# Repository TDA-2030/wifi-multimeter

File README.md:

# WiFi Multimeter

A mini multimeter based on ESP32, that display the result on web page.

## Features

- Web page as monitor

- Portable, small size

- Voice announcements

## Functions

  - voltage: ±400V, ±60V, ±2V

  - current: ±10A, ±2A, ±10mA

  - resistance: 1KΩ, 200KΩ, 10MΩ

  - buzzer

  - power
  
  - diode drop voltage

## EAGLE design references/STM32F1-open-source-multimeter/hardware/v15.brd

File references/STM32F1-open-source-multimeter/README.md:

# STM32 OpenSource Multimeter
*see the article [here](http://embedblog.eu/?p=438) or the video [here](https://youtu.be/qQX5iS70-mg)*

## Specs (revision 1.5 - latest stable)
1. voltage measurement: ±60 V, ±6 V, ±600 mV, ±60 m ranges, with DC or RMS data acquisition
2. current measurement: ±250 or ±2500 mA ranges, again with DC or RMS
3. can measure voltage and current simultaneously and display the product, ie power
4. measures continuity and displays the resistance and voltage drop
5. can perform simple component testing
6. frequency measurement up to 10 MHz

Additional features: isolated USB serial port; ; 2 kB EEPROM; 4 bit expansion port; battery voltage measurement & charging via USB; firmware update via USB; integrated kickstand; hold function

*Note: when this project started, it used STM32F1. Now it uses STM32F3, but I cannot rename the repository, so I hope it won't mislead anyone.*

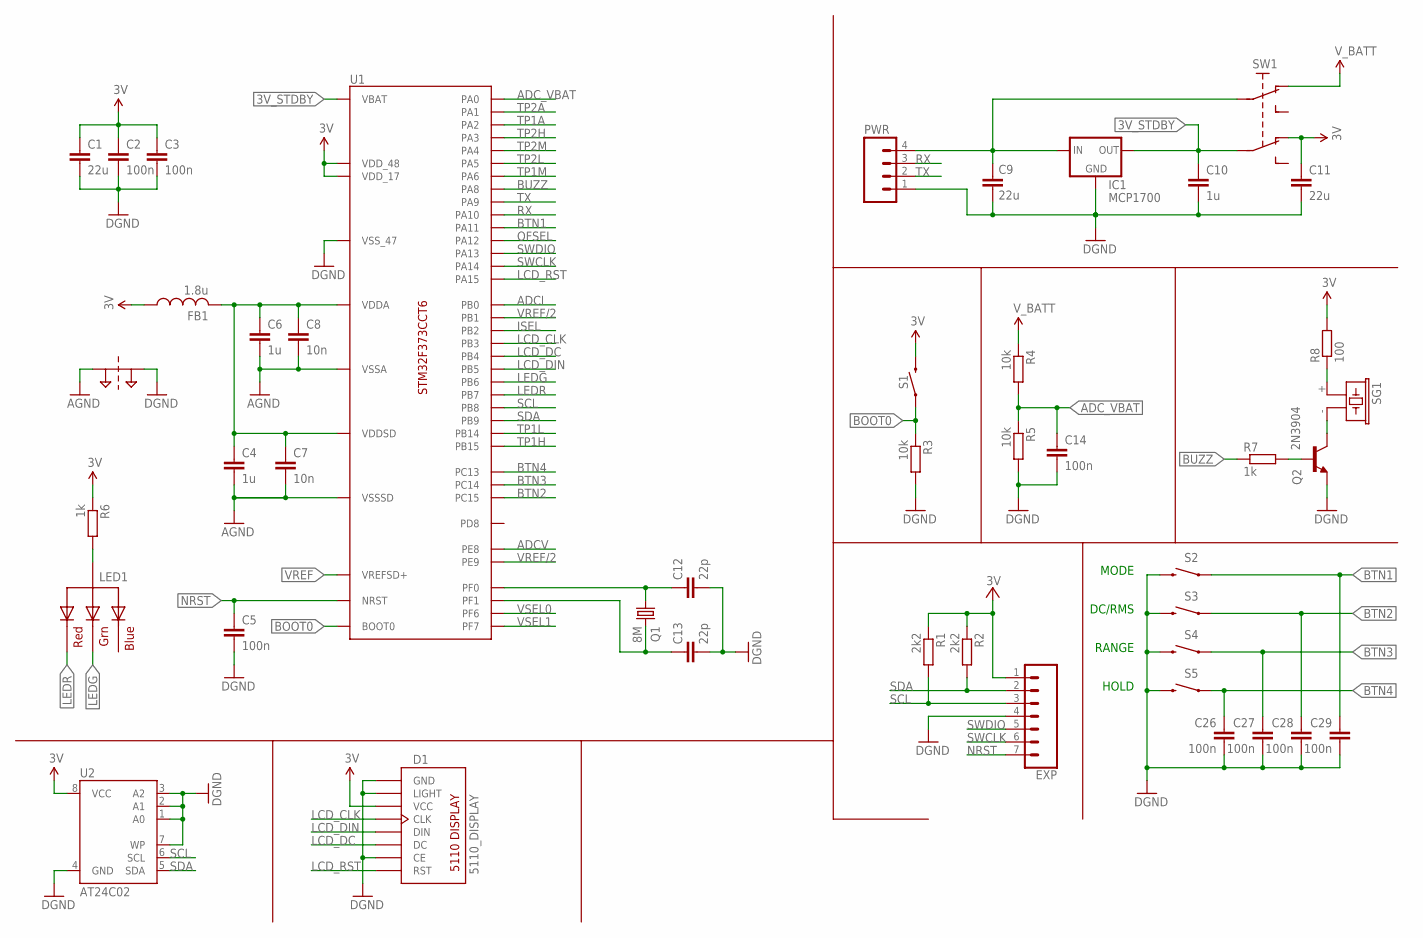
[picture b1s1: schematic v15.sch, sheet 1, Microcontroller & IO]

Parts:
C1, C9, C11: 22u; C1206
C2, C3, C5, C14, C26, C27, C28, C29: 100n; C1206
C4, C6, C10: 1u; C1206
C7, C8: 10n; C1206
C12, C13: 22p; C1206
D1: 5110_DISPLAY; 5110_LAYOUT
EXP: CONN_07; 1X07
FB1: 1.8u; 1206
IC1: MCP1700; SOT23
LED1: RGBLED_CA-5MM; LED5MMRGB
PT1: 2PT_GND_TIE
PWR: M04PTH; 1X04@1
Q1: 8M; HC49U-V
Q2: 2N3904; SOT23
R1, R2: 2k2; R1206
R3, R4, R5: 10k; R1206
R6, R7: 1k; R1206
R8: 100; R1206
S1: MOMENTARY-SWITCH-SPST-PTH-6.0MM; TACTILE_SWITCH_PTH_6.0MM
S2, S3, S4, S5: MOMENTARY-SWITCH-SPST-SMD-12MM; TACTILE_SWITCH_SMD_12MM
SG1: F/CM12P
SW1: DPDT_SWITCH_SMALL; DPDT_SMALL
U1: STM32F373CCT6; LQFP-48
U2: AT24C02; SOIC8

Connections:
3V: C1.1, C2.1, C3.1, C11.1, D1.VCC, EXP.1, FB1.1, R1.1, R2.1, R6.1, R8.2, S1.3 (2), SW1.P$6 (NC2), U1.17 (VDD_17), U1.48 (VDD_48), U2.8 (VCC); also elsewhere on the board
3V_STDBY: C10.1, IC1.2 (OUT), SW1.P$5 (I2), U1.1 (VBAT)
ADCI: U1.18 (PB0); also elsewhere on the board
ADCV: U1.21 (PE8); also elsewhere on the board
ADC_VBAT: C14.1, R4.2, R5.1, U1.10 (PA0)
AGND: C4.2, C6.2, C7.2, C8.2, PT1.P$1, U1.8 (VSSA), U1.23 (VSSSD); also elsewhere on the board
BOOT0: R3.1, S1.1, U1.44 (BOOT0)
BTN1: C29.1, S2.1, U1.32 (PA11)
BTN2: C28.1, S3.1, U1.4 (PC15)
BTN3: C27.1, S4.1, U1.3 (PC14)
BTN4: C26.1, S5.1, U1.2 (PC13)
BUZZ: R7.1, U1.29 (PA8)
GND: C1.2, C2.2, C3.2, C5.2, C9.2, C10.2, C11.2, C12.2, C13.2, C14.2, C26.2, C27.2, C28.2, C29.2, D1.CE, D1.GND, D1.LIGHT, EXP.4, IC1.1 (GND), PT1.P$2, PWR.1, Q2.2 (E), R3.2, R5.2, S2.3 (2), S3.3 (2), S4.3 (2), S5.3 (2), U1.47 (VSS_47), U2.1 (A0), U2.2 (A1), U2.3 (A2), U2.4 (GND), U2.7 (WP)
ISEL: U1.20 (PB2); also elsewhere on the board
LCD_CLK: D1.CLK, U1.39 (PB3)
LCD_DC: D1.DC, U1.40 (PB4)
LCD_DIN: D1.DIN, U1.41 (PB5)
LCD_RST: D1.RST, U1.38 (PA15)
LEDG: LED1.3 (GREEN), U1.42 (PB6)
LEDR: LED1.1 (RED), U1.43 (PB7)
unnamed: C12.1, Q1.1, U1.5 (PF0)
unnamed: C4.1, C6.1, C7.1, C8.1, FB1.2, U1.9 (VDDA), U1.24 (VDDSD)
unnamed: C9.1, IC1.3 (IN), PWR.4, SW1.P$2 (I1)
unnamed: LED1.2 (VCC), R6.2
unnamed: R8.1, SG1.+ (1)
unnamed: C13.1, Q1.2, U1.6 (PF1)
unnamed: Q2.3 (C), SG1.- (2)
unnamed: Q2.1 (B), R7.2
NRST: C5.1, EXP.7, U1.7 (NRST)
OFSEL: U1.33 (PA12); also elsewhere on the board
RX: PWR.3, U1.31 (PA10)
SCL: EXP.3, R1.2, U1.45 (PB8), U2.6 (SCL)
SDA: EXP.2, R2.2, U1.46 (PB9), U2.5 (SDA)
SWCLK: EXP.6, U1.37 (PA14)
SWDIO: EXP.5, U1.34 (PA13)
TP1A: U1.12 (PA2); also elsewhere on the board
TP1H: U1.27 (PB15); also elsewhere on the board
TP1L: U1.26 (PB14); also elsewhere on the board
TP1M: U1.16 (PA6); also elsewhere on the board
TP2A: U1.11 (PA1); also elsewhere on the board
TP2H: U1.13 (PA3); also elsewhere on the board
TP2L: U1.15 (PA5); also elsewhere on the board
TP2M: U1.14 (PA4); also elsewhere on the board
TX: PWR.2, U1.30 (PA9)
VREF: U1.25 (VREFSD+); also elsewhere on the board
VREF/2: U1.19 (PB1), U1.22 (PE9); also elsewhere on the board
VSEL0: U1.35 (PF6); also elsewhere on the board
VSEL1: U1.36 (PF7); also elsewhere on the board
V_BATT: R4.1, SW1.P$1 (NC1)

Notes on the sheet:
MODE
RANGE
DC/RMS
HOLD

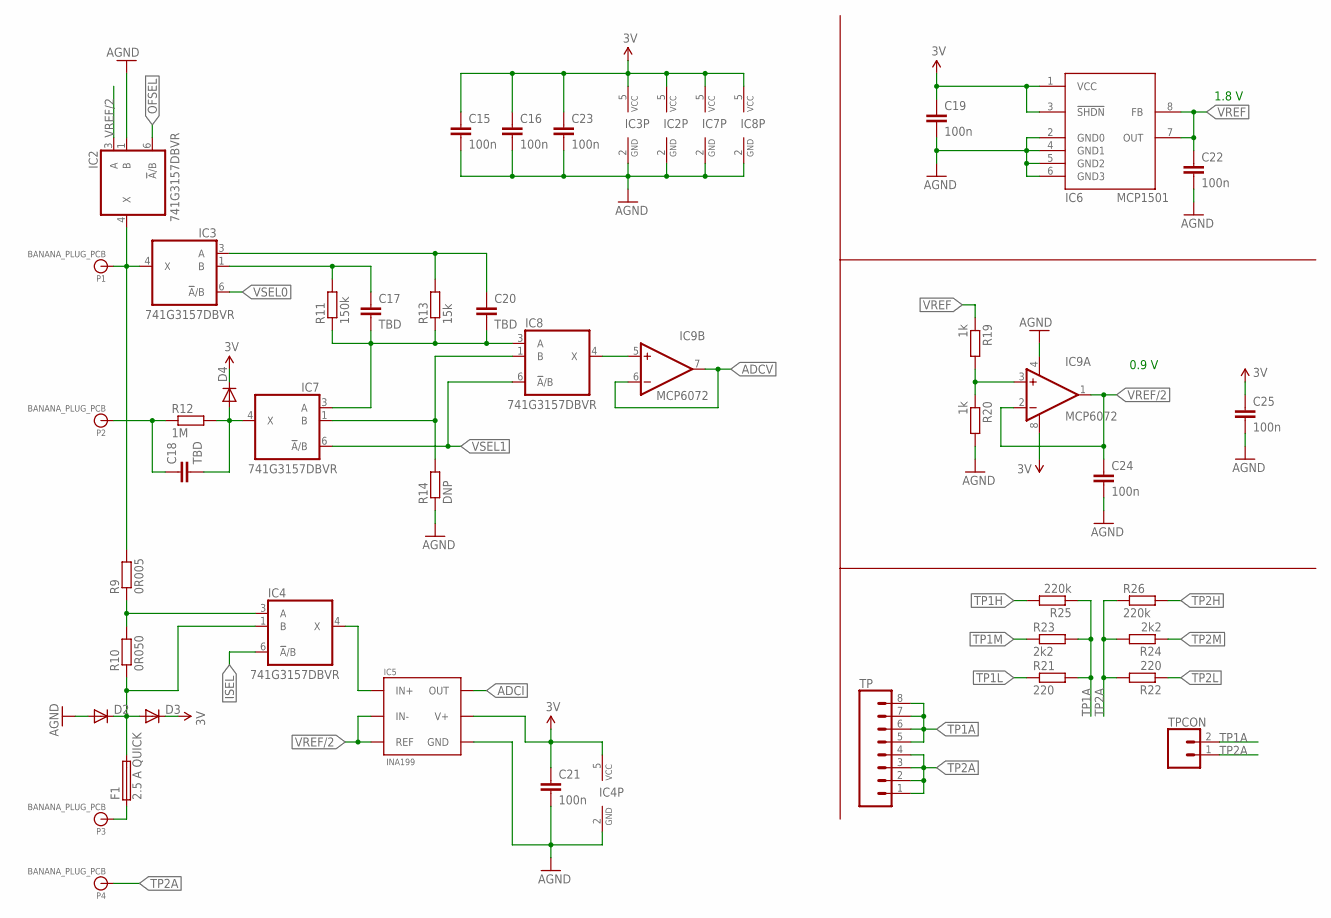
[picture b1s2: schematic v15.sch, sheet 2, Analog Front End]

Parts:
C15, C16, C21, C23: 100n; 1206
C17, C18, C20: TBD; 1206
C19, C22, C24, C25: 100n; C1206
D2, D3, D4: DIODE-MINIMELF; MINIMELF
F1: 2.5 A QUICK; SHK20L
IC2, IC3, IC4, IC7, IC8: 741G3157DBVR; DBV_R-PDSO-G6
IC5: INA199; SC70-6
IC6: MCP1501; SO08
IC9: MCP6072; SO08
P1, P2, P3, P4: BANANA_PLUG_PCB; BANANA_6MMHOLE
R9: 0R005; R1206
R10: 0R050; R1206
R11: 150k; R1206
R12: 1M; R1206
R13: 15k; R1206
R14: DNP; R1206
R19, R20: 1k; R1206
R21, R22: 220; R1206
R23, R24: 2k2; R1206
R25, R26: 220k; R1206
TP: CONN_08SMD-STRAIGHT-FEMALE; 1X08_SMD
TPCON: CONN_02; 1X02

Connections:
3V: C15.1, C16.1, C19.1, C21.1, C23.1, C25.1, D3.C, D4.C, IC2.5 (VCC), IC3.5 (VCC), IC4.5 (VCC), IC5.3 (V+), IC6.1 (VCC), IC6.3 (!SHDN), IC7.5 (VCC), IC8.5 (VCC), IC9.8 (V+); also elsewhere on the board
ADCI: IC5.6 (OUT); also elsewhere on the board
ADCV: IC9.6 (-IN), IC9.7 (OUT); also elsewhere on the board
AGND: C15.2, C16.2, C19.2, C21.2, C22.2, C23.2, C24.2, C25.2, D2.A, IC2.1 (B), IC2.2 (GND), IC3.2 (GND), IC4.2 (GND), IC5.2 (GND), IC6.2 (GND0), IC6.4 (GND1), IC6.5 (GND2), IC6.6 (GND3), IC7.2 (GND), IC8.2 (GND), IC9.4 (V-), R14.1, R20.2; also elsewhere on the board
COM: IC2.4 (X), IC3.4 (X), P1.P$1, R9.2
ISEL: IC4.6 (!A!/B); also elsewhere on the board
unnamed: C18.1, P2.P$1, R12.1
unnamed: C17.1, IC3.1 (B), R11.2
unnamed: C20.1, IC3.3 (A), R13.2
unnamed: C18.2, D4.A, IC7.4 (X), R12.2
unnamed: IC4.3 (A), R9.1, R10.2
unnamed: C17.2, C20.2, IC7.3 (A), IC8.3 (A), R11.1, R13.1
unnamed: D2.C, D3.A, F1.2A (2), IC4.1 (B), R10.1
unnamed: IC8.4 (X), IC9.5 (+IN)
unnamed: IC7.1 (B), IC8.1 (B), R14.2
unnamed: IC9.3 (+IN), R19.2, R20.1
unnamed: IC4.4 (X), IC5.4 (IN+)
unnamed: F1.1A (1), P3.P$1
OFSEL: IC2.6 (!A!/B); also elsewhere on the board
TP1A: R21.2, R23.2, R25.1, TP.5, TP.6, TP.7, TP.8, TPCON.2; also elsewhere on the board
TP1H: R25.2; also elsewhere on the board
TP1L: R21.1; also elsewhere on the board
TP1M: R23.1; also elsewhere on the board
TP2A: P4.P$1, R22.2, R24.2, R26.1, TP.1, TP.2, TP.3, TP.4, TPCON.1; also elsewhere on the board
TP2H: R26.2; also elsewhere on the board
TP2L: R22.1; also elsewhere on the board
TP2M: R24.1; also elsewhere on the board
VREF: C22.1, IC6.7 (OUT), IC6.8 (FB), R19.1; also elsewhere on the board
VREF/2: C24.1, IC2.3 (A), IC5.1 (REF), IC5.5 (IN-), IC9.1 (OUT), IC9.2 (-IN); also elsewhere on the board
VSEL0: IC3.6 (!A!/B); also elsewhere on the board
VSEL1: IC7.6 (!A!/B), IC8.6 (!A!/B); also elsewhere on the board

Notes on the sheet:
1.8 V
0.9 V

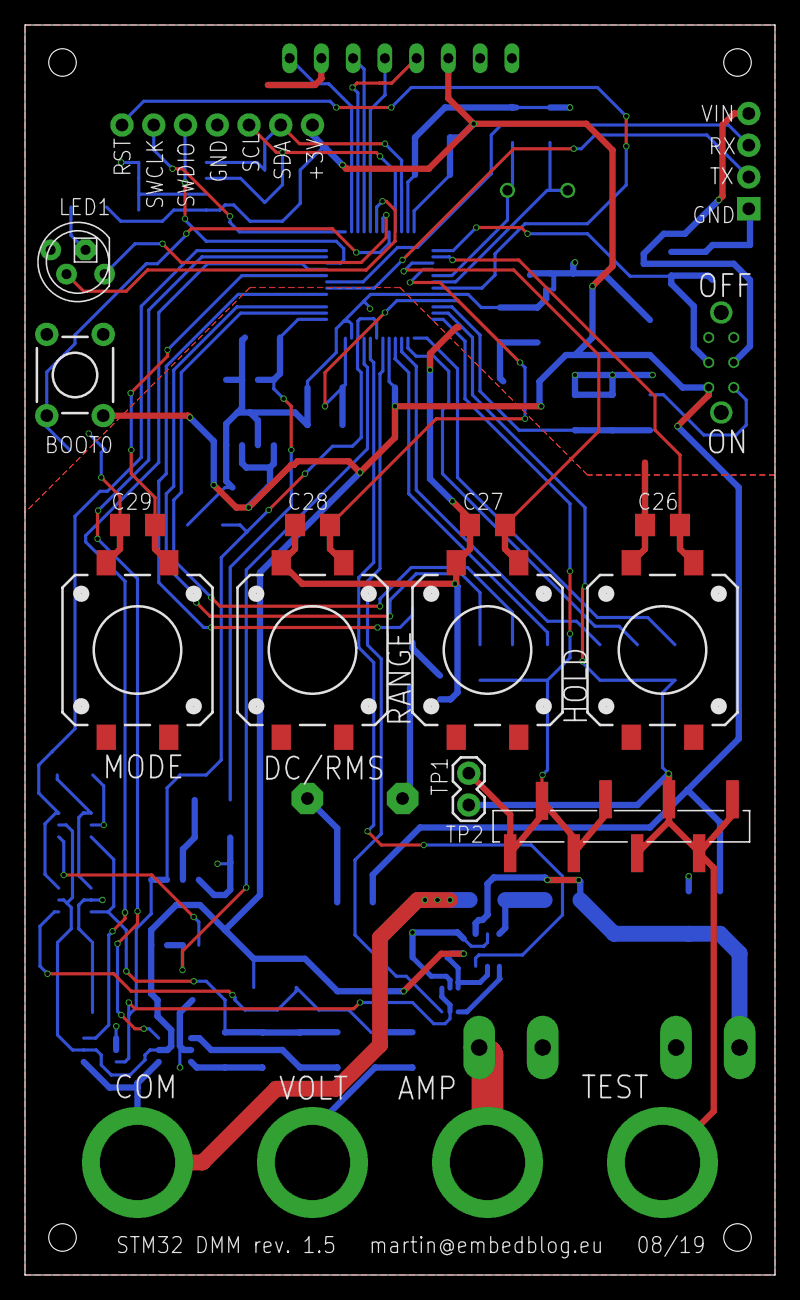
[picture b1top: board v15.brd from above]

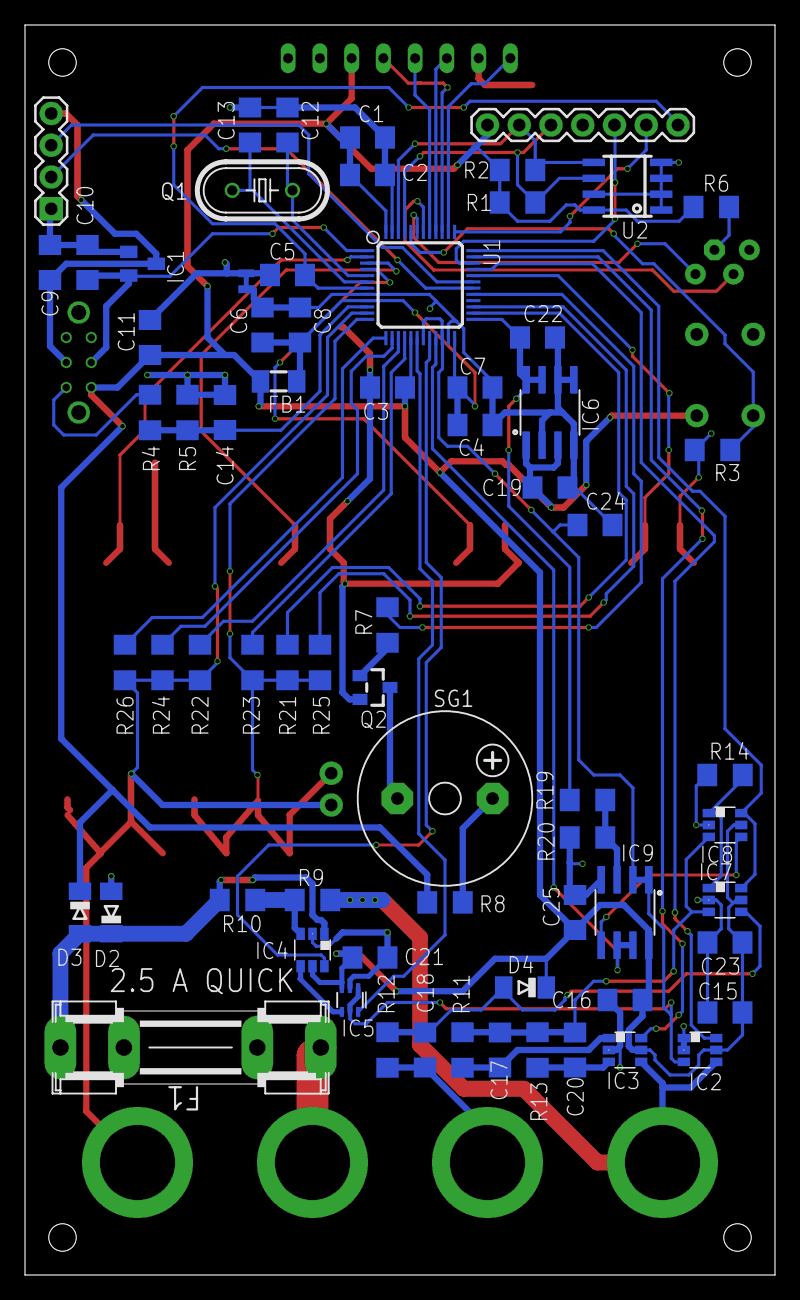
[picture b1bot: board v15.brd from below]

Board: 2 copper layers, 60.0 x 100.0 mm, 87 parts (69 on the bottom side), 62 nets.

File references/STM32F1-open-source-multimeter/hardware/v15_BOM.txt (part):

Part  Value                           Device                          Package                  Description                                                                                                     MF MPN OC_FARNELL OC_NEWARK PROD_ID     SF_ID     SF_SKU   
C1    22u                             C-EUC1206                       C1206                    CAPACITOR, European symbol                                                                                                                                                 
C2    100n                            C-EUC1206                       C1206                    CAPACITOR, European symbol                                                                                                                                                 
C3    100n                            C-EUC1206                       C1206                    CAPACITOR, European symbol                                                                                                                                                 
C4    1u                              C-EUC1206                       C1206                    CAPACITOR, European symbol                                                                                                                                                 
C5    100n                            C-EUC1206                       C1206                    CAPACITOR, European symbol                                                                                                                                                 
C6    1u                              C-EUC1206                       C1206                    CAPACITOR, European symbol                                                                                                                                                 
C7    10n                             C-EUC1206                       C1206                    CAPACITOR, European symbol                                                                                                                                                 
C8    10n                             C-EUC1206                       C1206                    CAPACITOR, European symbol                                                                                                                                                 
C9    22u                             C-EUC1206                       C1206                    CAPACITOR, European symbol                                                                                                                                                 
C10   1u                              C-EUC1206                       C1206                    CAPACITOR, European symbol                                                                                                                                                 
C11   22u                             C-EUC1206                       C1206                    CAPACITOR, European symbol                                                                                                                                                 
C12   22p                             C-EUC1206                       C1206                    CAPACITOR, European symbol                                                                                                                                                 
C13   22p                             C-EUC1206                       C1206                    CAPACITOR, European symbol                                                                                                                                                 
C14   100n                            C-EUC1206                       C1206                    CAPACITOR, European symbol                                                                                                                                                 
C15   100n                            CAP1206                         1206                     Capacitor                                                                                                                                                                  
C16   100n                            CAP1206                         1206                     Capacitor                                                                                                                                                                  
C17   TBD                             CAP1206                         1206                     Capacitor                                                                                                                                                                  
C18   TBD                             CAP1206                         1206                     Capacitor                                                                                                                                                                  
C19   100n                            C-EUC1206                       C1206                    CAPACITOR, European symbol                                                                                                                                                 
C20   TBD                             CAP1206                         1206                     Capacitor                                                                                                                                                                  
C21   100n                            CAP1206                         1206                     Capacitor                                                                                                                                                                  
C22   100n                            C-EUC1206                       C1206                    CAPACITOR, European symbol                                                                                                                                                 
C23   100n                            CAP1206                         1206                     Capacitor                                                                                                                                                                  
C24   100n                            C-EUC1206                       C1206                    CAPACITOR, European symbol                                                                                                                                                 
C25   100n                            C-EUC1206                       C1206                    CAPACITOR, European symbol                                                                                                                                                 
C26   100n                            C-EUC1206                       C1206                    CAPACITOR, European symbol                                                                                                                                                 
C27   100n                            C-EUC1206                       C1206                    CAPACITOR, European symbol                                                                                                                                                 
C28   100n                            C-EUC1206                       C1206                    CAPACITOR, European symbol                                                                                                                                                 
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
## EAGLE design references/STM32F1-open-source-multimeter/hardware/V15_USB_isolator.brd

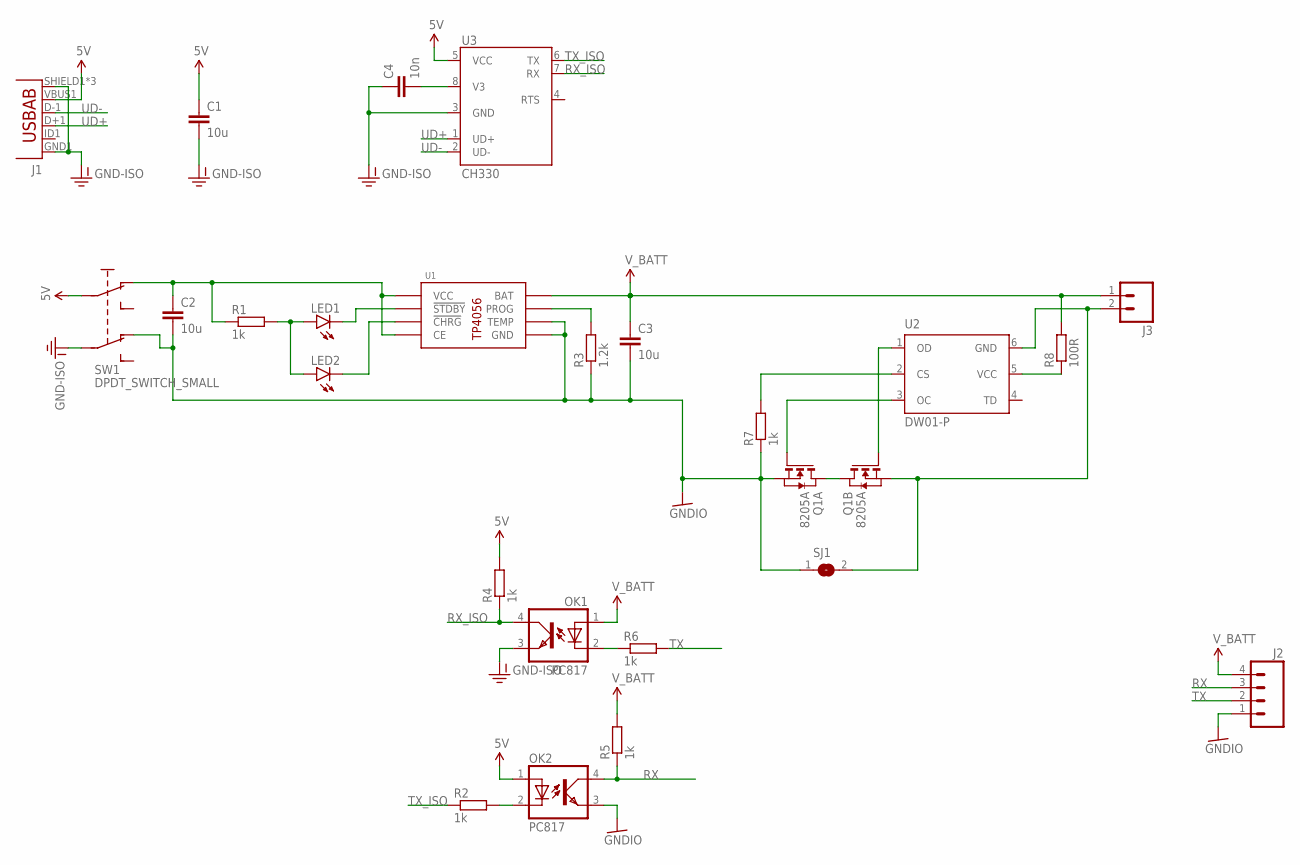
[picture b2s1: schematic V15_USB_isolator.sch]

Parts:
C1, C2, C3: 10u; C1206
C4: 10n; C1206
J1: USB-ABCONN-11794; USB-AB-MICRO-SMD_V03
J2: M04PTH; 1X04@1
J3: M02PTH3; 1X02_LONGPADS
LED1, LED2: LED1206-BOTTOM; LED-1206-BOTTOM
OK1, OK2: PC817; DIL04
Q1: 8205A; TSSOP8
R1, R2, R4, R5, R6, R7: 1k; R1206
R3: 1.2k; R1206
R8: 100R; R1206
SJ1: SJ
SW1: DPDT_SWITCH_SMALL; DPDT_SMALL
U1: TP4056; SOP8
U2: DW01-P; SOT23-6L
U3: CH330; SO08

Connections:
5V: C1.1, J1.VBUS1 (VBUS), OK2.1 (A), R4.2, SW1.P$2 (I1), U3.5 (VCC)
5V_ISO: C2.1, R1.1, SW1.P$1 (NC1), U1.4 (VCC), U1.8 (CE)
GND-ISO: C1.2, C4.1, J1.GND1 (GND), J1.SHIELD1 (SHIELD), J1.SHIELD2 (SHIELD), J1.SHIELD3 (SHIELD), OK1.3 (EMIT), SW1.P$5 (I2), U3.3 (GND)
GNDIO: C2.2, C3.2, J2.1, OK2.3 (EMIT), Q1.2 (S), Q1.3 (S), R3.1, R7.1, SJ1.1, SW1.P$6 (NC2), U1.1 (TEMP), U1.3 (GND)
unnamed: C4.2, U3.8 (V3)
unnamed: Q1.1 (D), Q1.8 (D)
unnamed: LED1.A, LED2.A, R1.2
unnamed: LED1.C, U1.6 (!STDBY)
unnamed: LED2.C, U1.7 (!CHRG)
unnamed: R3.2, U1.2 (PROG)
unnamed: OK2.2 (C), R2.2
unnamed: OK1.2 (C), R6.1
unnamed: R8.1, U2.5 (VCC)
unnamed: J3.2, Q1.6 (S), Q1.7 (S), SJ1.2, U2.6 (GND)
unnamed: Q1.5 (G), U2.1 (OD)
unnamed: Q1.4 (G), U2.3 (OC)
unnamed: R7.2, U2.2 (CS)
RX: J2.3, OK2.4 (COL), R5.1
RX_ISO: OK1.4 (COL), R4.1, U3.7 (RX)
TX: J2.2, R6.2
TX_ISO: R2.1, U3.6 (TX)
UD+: J1.D+1 (D+), U3.1 (UD+)
UD-: J1.D-1 (D-), U3.2 (UD-)
V_BATT: C3.1, J2.4, J3.1, OK1.1 (A), R5.2, R8.2, U1.5 (BAT)

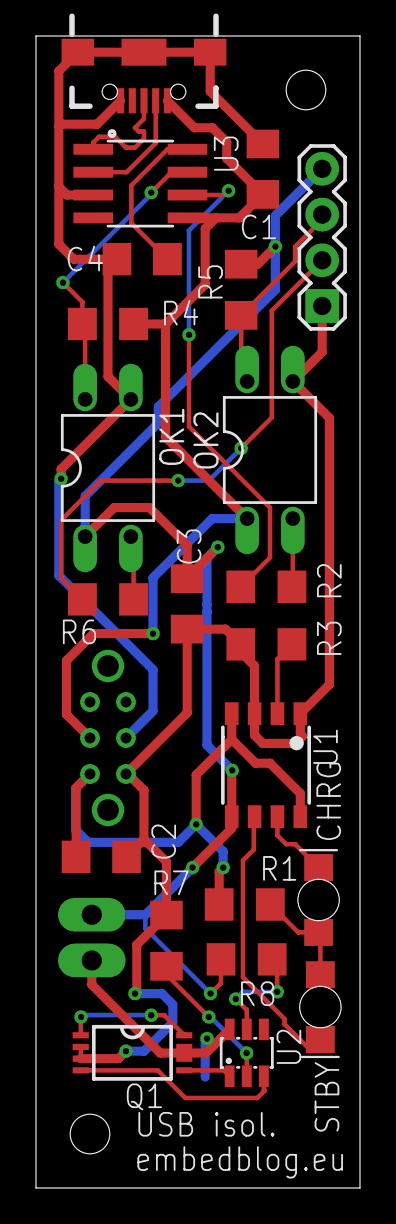
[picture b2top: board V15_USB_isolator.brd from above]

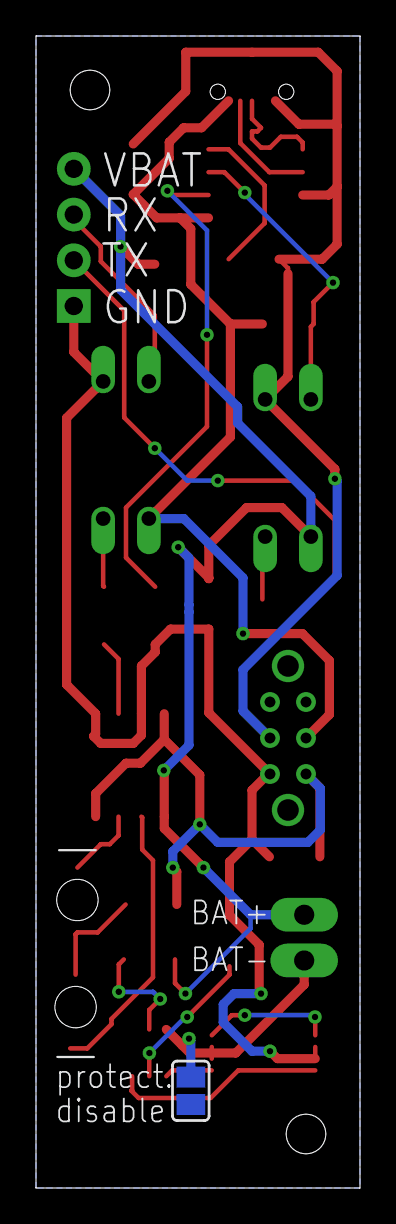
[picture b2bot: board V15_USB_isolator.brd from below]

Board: 2 copper layers, 18.0 x 64.0 mm, 25 parts (2 on the bottom side), 24 nets.

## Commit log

2020-07-24 feat: add wed page
2020-07-24 fix: update favicon
2020-07-25 feat: add web page 4 button
2020-07-26 feat: add speech files
2020-07-27 fix: add gitignore for folder speech
2020-07-27 feat: add speech
2020-07-27 feat: add speech list
2020-07-29 feat: first complete speech
2020-07-29 feat: add file manage
2020-07-30 feat: add settings page
2020-07-30 fix: remove the redundant audio files
2020-07-30 feat: add PCB files
2020-08-02 feat: add ADS1115 and INA226 code
2020-08-02 feat: add reference files
2020-08-03 fix: ADS1115
2020-08-16 update pcb
2020-08-19 fix: i2c_bus and ina226
2020-08-21 fix: update speech play string
2020-08-22 feat: add check audio file is updated
2020-08-22 fix: speech string issue
2020-08-22 style: rename components web to web-dashboard
2021-02-04 fix: replace blufi with webconfig
2021-02-04 add simulation folder
2021-02-06 draft

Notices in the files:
parts and their libraries:
SparkFun-Connectors: Licensing: Creative Commons ShareAlike 4.0 International - https://creativecommons.org/licenses/by-sa/4.0
m-pad-2.1: License : GNU General Public License version 2 (see bottom)
